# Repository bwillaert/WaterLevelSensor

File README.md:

# WaterLevelSensor
Capacitive water level sensor

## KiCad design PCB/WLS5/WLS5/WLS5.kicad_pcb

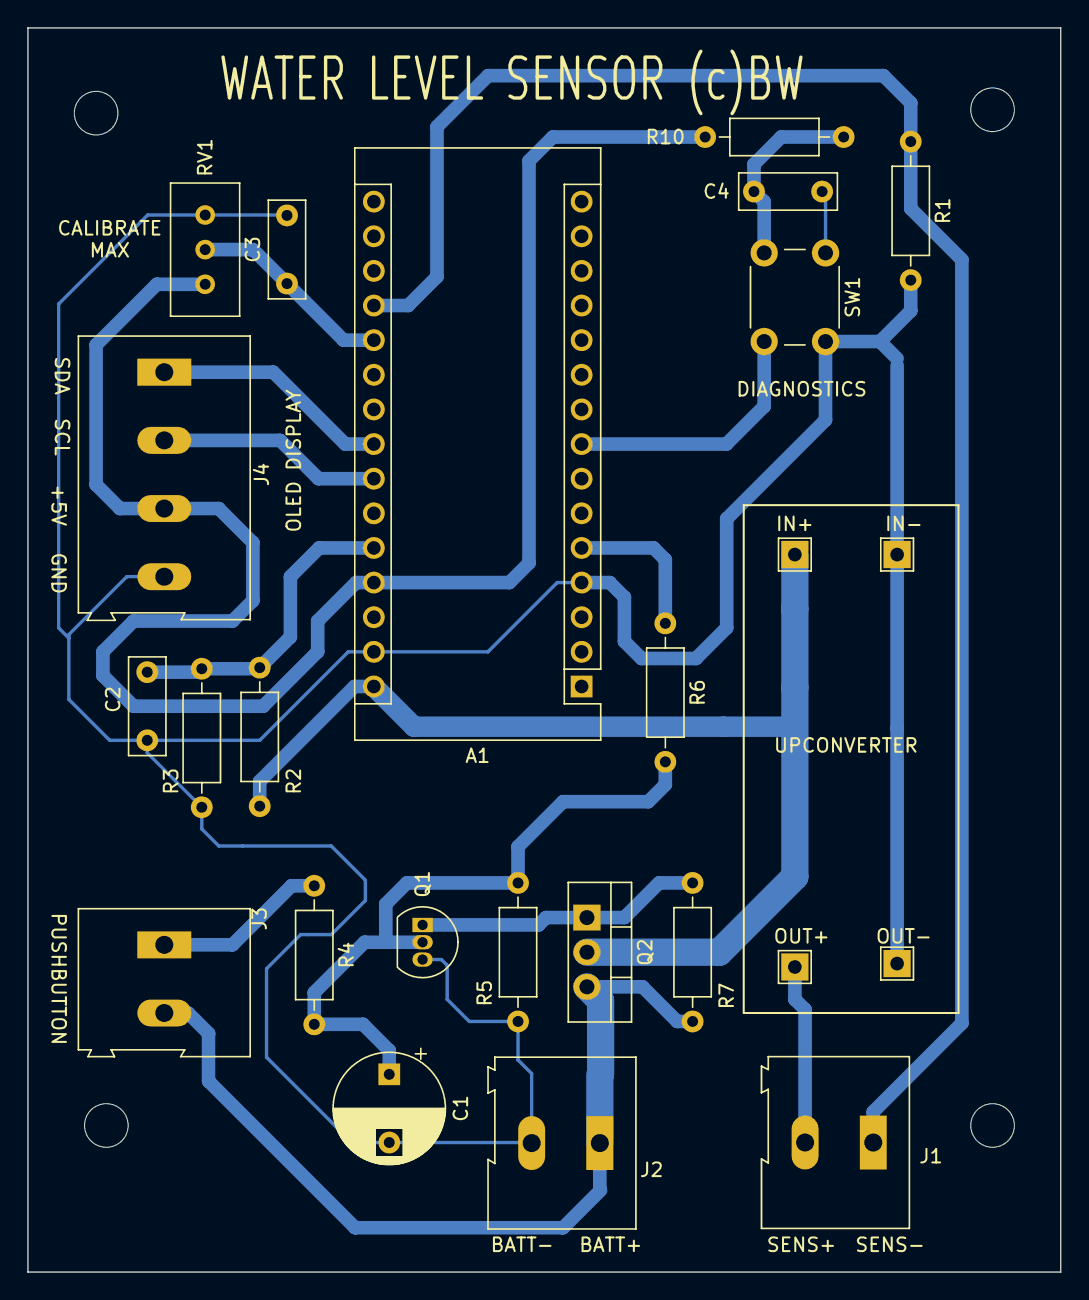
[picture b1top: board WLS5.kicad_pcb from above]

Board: 2 copper layers, 75.8 x 91.2 mm, 29 parts (0 on the bottom side), 15 nets.

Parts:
A1: Arduino_Nano_Every; Arduino_Nano
C1: 100M; CP_Radial_D8.0mm_P5.00mm
C2, C3, C4: 100n; C_Disc_D7.0mm_W2.5mm_P5.00mm
H1, H2, H3, H4: MountingHole; MountingHole_3.2mm_M3
IN+: IN+; TestPoint_THTPad_2.0x2.0mm_Drill1.0mm
IN-: IN-; TestPoint_THTPad_2.0x2.0mm_Drill1.0mm
J1: Sensor; TerminalBlock_Altech_AK300-2_P5.00mm
J2: Battery; TerminalBlock_Altech_AK300-2_P5.00mm
J3: PushButton; TerminalBlock_Altech_AK300-2_P5.00mm
J4: OLED Display; TerminalBlock_Altech_AK300-4_P5.00mm
OUT+: UP+; TestPoint_THTPad_2.0x2.0mm_Drill1.0mm
OUT-: UP-; TestPoint_THTPad_2.0x2.0mm_Drill1.0mm
Q1: BC547; TO-92_Inline
Q2: IRF9540N; TO-220-3_Vertical
R1: 220E; R_Axial_DIN0207_L6.3mm_D2.5mm_P10.16mm_Horizontal
R2: 33K; R_Axial_DIN0207_L6.3mm_D2.5mm_P10.16mm_Horizontal
R3, R10: 10K; R_Axial_DIN0207_L6.3mm_D2.5mm_P10.16mm_Horizontal
R4, R6: 1K; R_Axial_DIN0207_L6.3mm_D2.5mm_P10.16mm_Horizontal
R5, R7: 47K; R_Axial_DIN0207_L6.3mm_D2.5mm_P10.16mm_Horizontal
RV1: Calibrate max; Potentiometer_Bourns_3296W_Vertical
SW1: DIAGNOSTICS; SW_PUSH_6mm

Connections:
+5V: A1.27 (+5V), J4.3, R10.1, RV1.1
+9V: J2.1, J3.2, Q2.3 (S), R7.1
+9VA: A1.30 (VIN), IN+.1, Q2.2 (D), R2.1
GND: A1.4 (GND), A1.29 (GND), C1.2, C2.2, C3.2, C4.2, IN-.1, J2.2, J4.4, OUT-.1, Q1.3 (E), R1.2, R3.2, R5.2, RV1.3, SW1.1
unnamed: A1.5 (D2), R6.1
unnamed: A1.8 (D5), C4.1, R10.2, SW1.2
unnamed: A1.20 (A1), C3.1, RV1.2
unnamed: A1.23 (SDA/A4), J4.1
unnamed: A1.24 (SCL/A5), J4.2
unnamed: A1.26 (A7), C2.1, R2.2, R3.1
unnamed: C1.1, Q1.2 (B), R4.2, R5.1, R6.2
unnamed: A1.19 (A0), J1.1, R1.1
unnamed: J3.1, R4.1
unnamed: J1.2, OUT+.1
unnamed: Q1.1 (C), Q2.1 (G), R7.2

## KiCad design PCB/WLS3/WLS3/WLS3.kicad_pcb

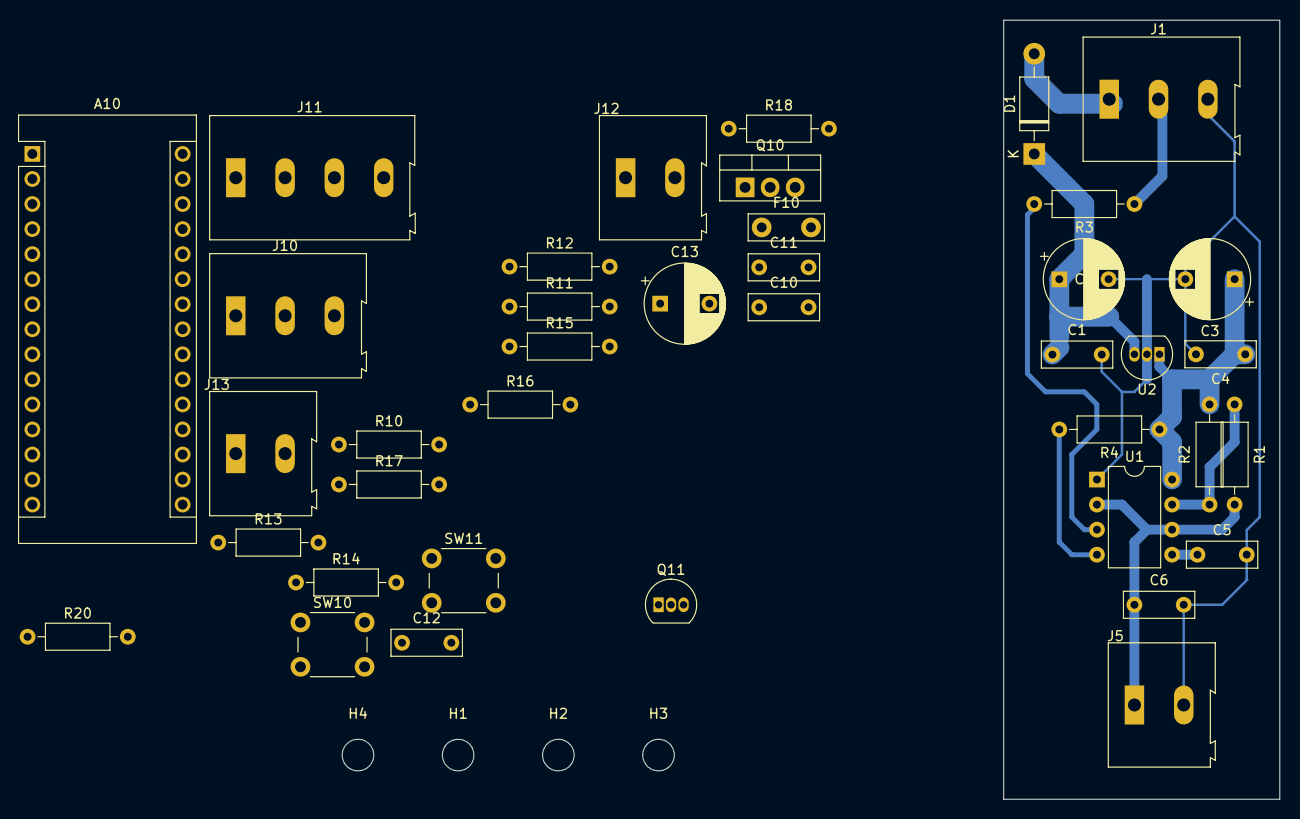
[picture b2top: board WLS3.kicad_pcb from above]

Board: 2 copper layers, 28.0 x 79.0 mm, 43 parts (0 on the bottom side), 27 nets.

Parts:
A10: Arduino_Nano_Every; Arduino_Nano
C1, C4, C10, C11, C12: 100n; C_Disc_D7.0mm_W2.5mm_P5.00mm
C2, C3, C13: 100M; CP_Radial_D8.0mm_P5.00mm
C5: 10n; C_Disc_D7.0mm_W2.5mm_P5.00mm
C6: 22p; C_Disc_D7.0mm_W2.5mm_P5.00mm
D1: 1N4001; D_DO-41_SOD81_P10.16mm_Horizontal
F10: 100mA; C_Disc_D7.5mm_W2.5mm_P5.00mm
H1, H2, H3, H4: MountingHole; MountingHole_3.2mm_M3
J1, J10: Sensor; TerminalBlock_Altech_AK300-3_P5.00mm
J5: Sensor Wire; TerminalBlock_Altech_AK300-2_P5.00mm
J11: OLED Display; TerminalBlock_Altech_AK300-4_P5.00mm
J12: Battery; TerminalBlock_Altech_AK300-2_P5.00mm
J13: PushButton; TerminalBlock_Altech_AK300-2_P5.00mm
Q10: IRF9540N; TO-220-3_Vertical
Q11: BC547; TO-92_Inline
R1, R11, R12, R14: 10K; R_Axial_DIN0207_L6.3mm_D2.5mm_P10.16mm_Horizontal
R2: 100K; R_Axial_DIN0207_L6.3mm_D2.5mm_P10.16mm_Horizontal
R3, R10, R20: 100E; R_Axial_DIN0207_L6.3mm_D2.5mm_P10.16mm_Horizontal
R4: 10E; R_Axial_DIN0207_L6.3mm_D2.5mm_P10.16mm_Horizontal
R13: 33K; R_Axial_DIN0207_L6.3mm_D2.5mm_P10.16mm_Horizontal
R15, R16: 1K; R_Axial_DIN0207_L6.3mm_D2.5mm_P10.16mm_Horizontal
R17, R18: 47K; R_Axial_DIN0207_L6.3mm_D2.5mm_P10.16mm_Horizontal
SW10: CAL DRY; SW_PUSH_6mm_H5mm
SW11: CAL WET; SW_PUSH_6mm_H5mm
U1: NE555P; DIP-8_W7.62mm
U2: LM78L05_TO92; TO-92_Inline

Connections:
+5V: A10.27 (+5V), J11.3, R11.1, R12.1
+5VA: C3.1, C4.1, R1.1, R4.1, U1.8 (VCC), U2.1 (VO)
+9V: J12.2, J13.2, Q10.3 (S), R18.1
+9VA: A10.30 (VIN), F10.1, Q10.2 (D), R13.1
GND: A10.4 (GND), A10.29 (GND), C10.2, C11.2, C12.2, C13.2, J10.1, J11.4, J12.1, Q11.3 (E), R14.2, R17.2, SW10.1, SW11.1
GNDA: C1.2, C2.2, C3.2, C4.2, C5.2, C6.2, J1.3, J5.2, U1.1 (GND), U2.2 (GND)
unnamed: A10.2 (RX1), R20.2
unnamed: A10.5 (D2), R10.2
unnamed: A10.6 (D3), C10.1, R11.2, SW10.2
unnamed: A10.7 (D4), C11.1, R12.2, SW11.2
unnamed: A10.8 (D5), R16.1
unnamed: A10.19 (A0), C12.1, R13.2, R14.1
unnamed: A10.23 (SDA/A4), J11.1
unnamed: A10.24 (SCL/A5), J11.2
unnamed: C1.1, C2.1, D1.1 (K), U2.3 (VI)
unnamed: C5.1, U1.5 (CV)
unnamed: C6.1, J5.1, R2.2, U1.2 (TR), U1.6 (THR)
unnamed: C13.1, Q11.2 (B), R15.2, R16.2, R17.1
unnamed: D1.2 (A), J1.1
unnamed: F10.2, J10.3
unnamed: J10.2, R10.1, R20.1
unnamed: J13.1, R15.1
unnamed: Q10.1 (G), Q11.1 (C), R18.2
unnamed: R1.2, R2.1, U1.7 (DIS)
unnamed: J1.2, R3.1
unnamed: R4.2, U1.4 (R)
unnamed: R3.2, U1.3 (Q)

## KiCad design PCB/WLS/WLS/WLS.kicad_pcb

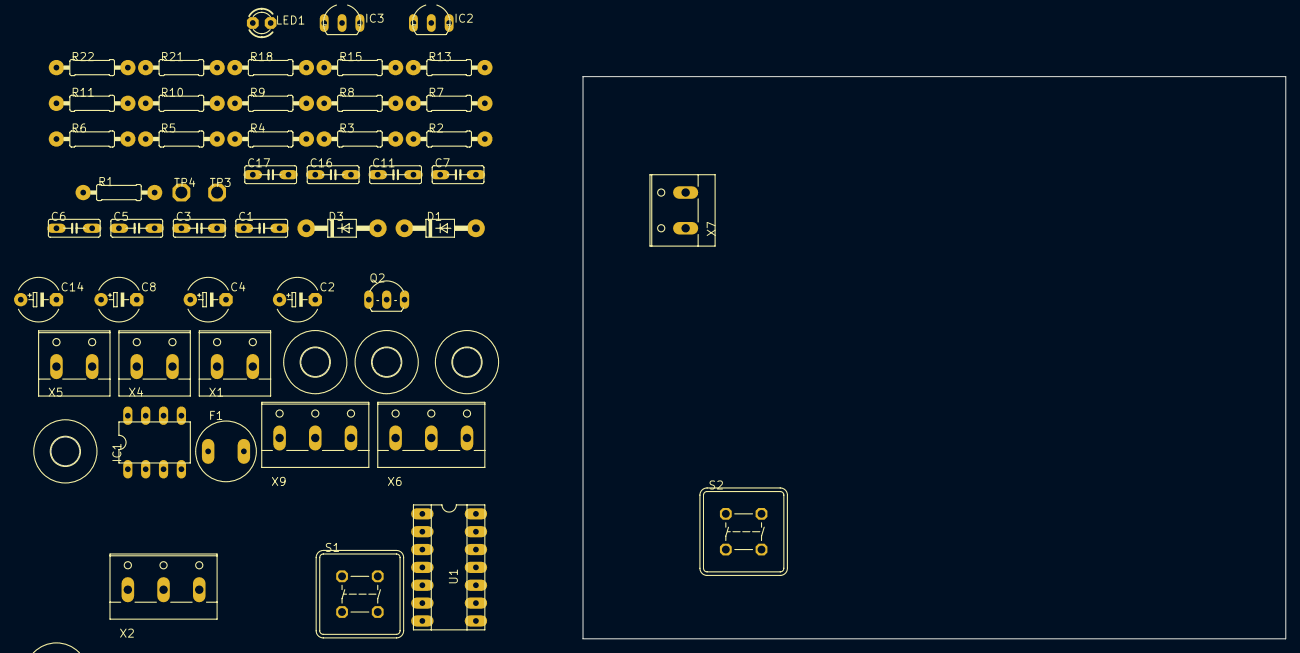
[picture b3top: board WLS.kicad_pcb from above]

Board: 2 copper layers, 100.0 x 80.0 mm, 56 parts (0 on the bottom side), 28 nets, no tracks yet.

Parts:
C1, C3, C5, C7, C11, C16, C17: 100n; C050-025X075
C2, C4, C8: 100µF; E5-6
C6: 10n; C050-025X075
C14: 10µF; E5-6
D1, D3: 1N4004; DO41-10
F1: 100mA; TR5
H1, H2, H3, H4, H5, H6, H7, H8: MOUNT-HOLE4.1; 4,1
IC1: NE555; DIL-08
IC2, IC3: 78L05; 78LXX
LED1: LED3MM
Q2: BS170; TO92-CBE
R1, R2, R11, R13, R22: 100K; 0207_10
R3, R6, R7, R10: 1K; 0207_10
R4, R5, R15: 47K; 0207_10
R8: 33K; 0207_10
R9: 10K; 0207_10
R18: 100E; 0207_10
R21: 10E; 0207_10
S1, S2: DTE6K
TP3, TP4: PTR1PAD1-17; P1-17
U1: PIC16F1824; DIP-14
X1, X4, X5, X7: W237-132
X2, X6, X9: W237-3E

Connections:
+5V: C4.+, C5.1, C14.+, C17.1, IC2.OUT, IC3.OUT, R4.2, R5.2, R15.2, U1.1
+12V: C2.+, C3.1, C8.+, C16.1, D1.C, D3.C, IC1.4, IC1.8, IC2.IN, IC3.IN, R8.2, R13.1, X2.3
GND: C2.-, C3.2, C4.-, C5.2, C6.1, C8.-, C14.-, C16.2, C17.2, F1.2, IC1.1, IC2.GND, IC3.GND, LED1.K, Q2.E, R9.1, R11.1, TP3.TP, U1.14, X1.2, X2.1, X5.1, X6.2, X7.2, X9.2
unnamed: IC1.2, IC1.6, R13.2, R18.2, R22.1, X7.1
unnamed: R21.2, U1.6
unnamed: IC1.3, R22.2
unnamed: C1.1, R4.1, S1.1, S1.2, U1.3
unnamed: R3.1, X2.2
unnamed: R3.2, U1.9
unnamed: R6.2, X9.3
unnamed: R7.2, X9.1
unnamed: R7.1, U1.7
unnamed: C11.1, R15.1, U1.4, X4.2
unnamed: R6.1, U1.11
unnamed: C6.2, IC1.5
unnamed: R10.2, U1.8
unnamed: R18.1, X6.1
unnamed: R1.1, R2.1, U1.5
unnamed: R1.2, R2.2, X5.2
unnamed: R8.1, R9.2, U1.12
unnamed: Q2.B, R11.2, R21.1
unnamed: D1.A, X6.3
unnamed: TP4.TP, U1.13
unnamed: LED1.A, R10.1
unnamed: F1.1, Q2.C
unnamed: C1.2, C7.2, C11.2, S1.3, S1.4, S2.3, S2.4, X4.1
unnamed: C7.1, R5.1, S2.1, S2.2, U1.2
unnamed: D3.A, X1.1

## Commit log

2021-08-24 WLS repo created
2021-08-24 WLS init
2021-08-24 Init
2021-08-24 Added WLS1
2021-08-24 Dev start
2022-05-05 Initial rework
2023-05-29 WaterLevelSensor repo init
2023-06-13 Updated PCB sensor
2023-09-03 Added WLS4 and WLS5
2023-09-22 Averaging the current sensor value
2023-12-21 Added manual
2023-12-21 Added arduino_for_dummies
2023-12-21 Added datasheet
